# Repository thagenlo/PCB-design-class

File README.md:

# PCB-design-class
2.S975 KiCAD repo

**Multimeter Project**

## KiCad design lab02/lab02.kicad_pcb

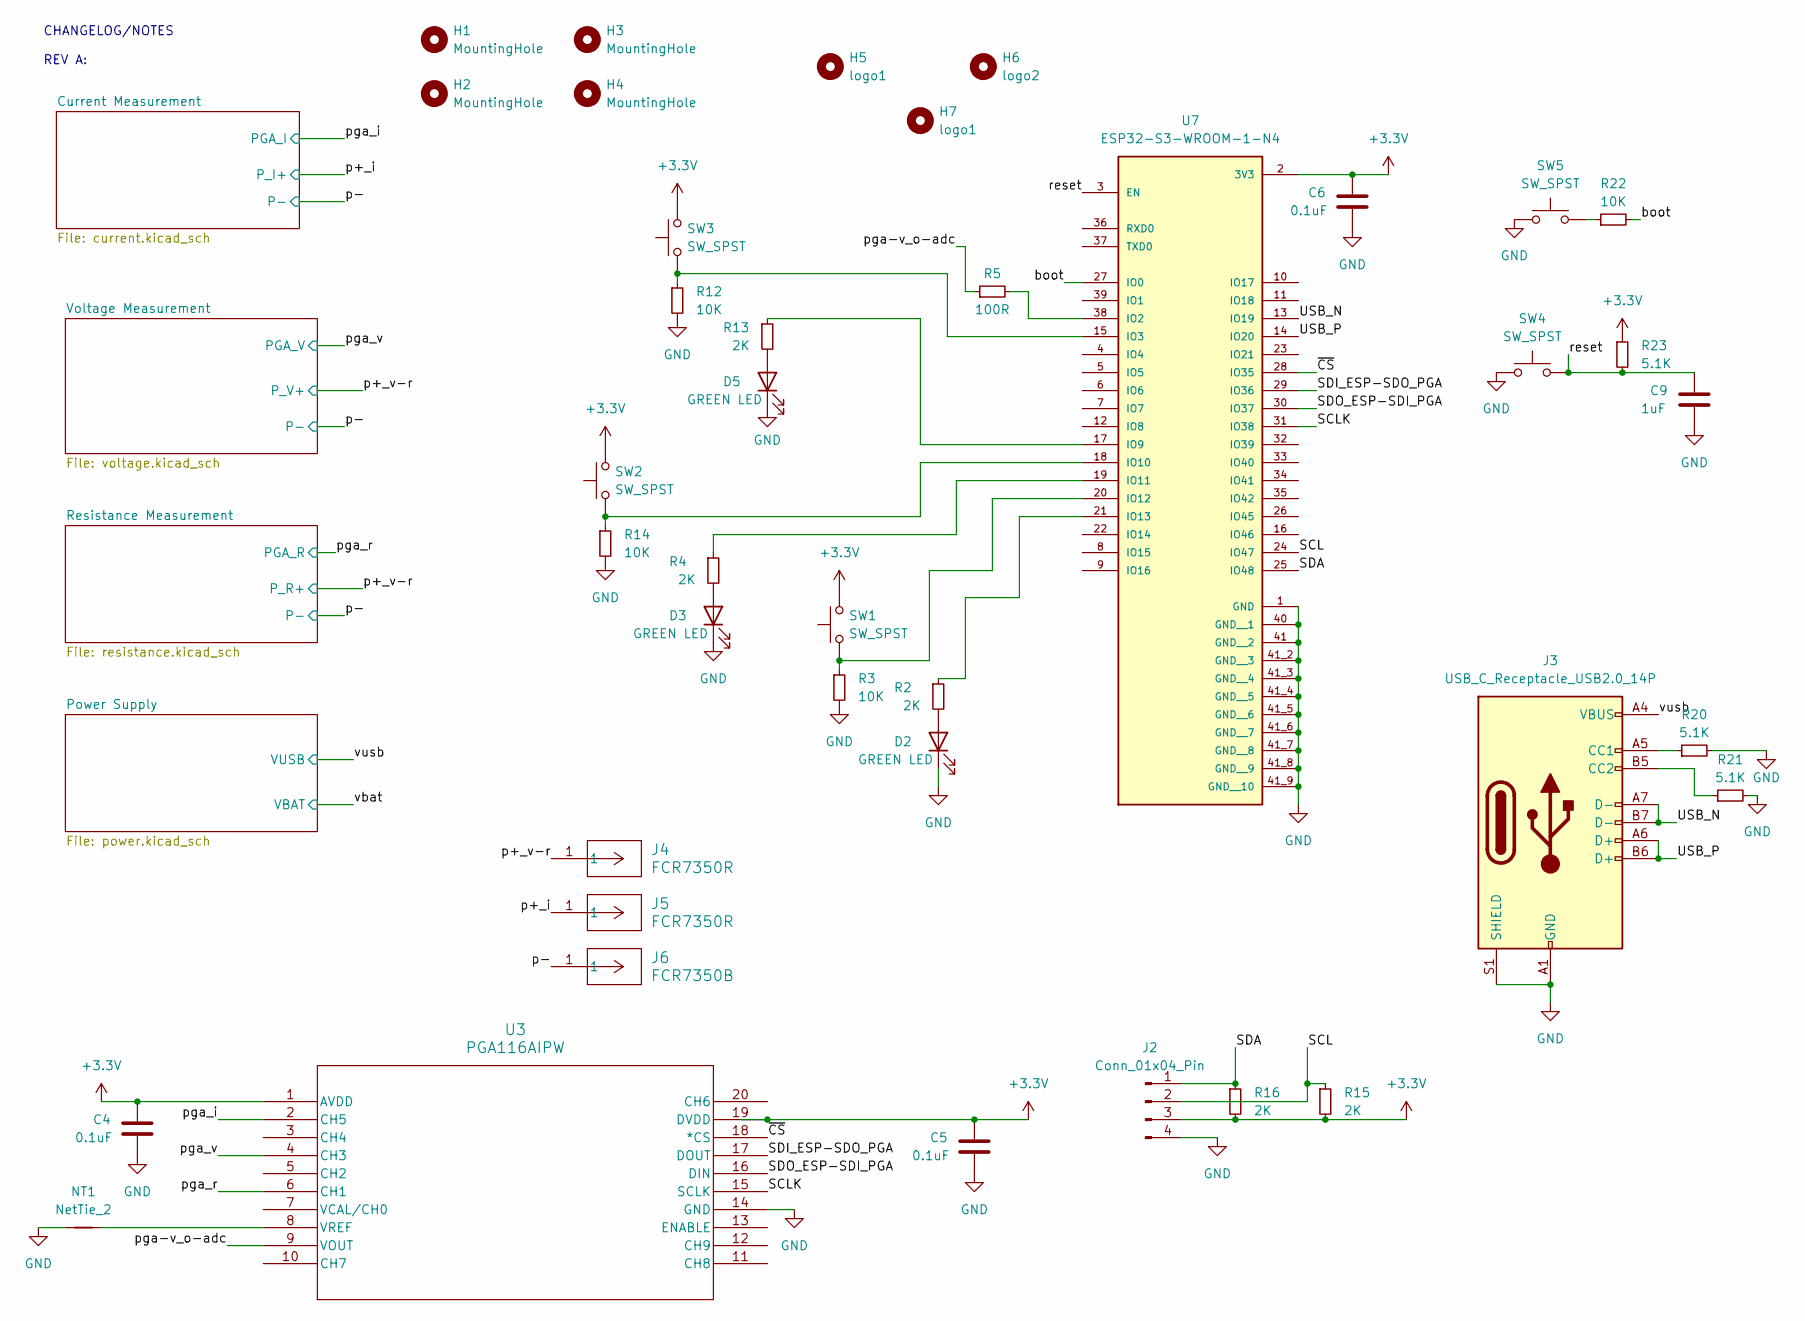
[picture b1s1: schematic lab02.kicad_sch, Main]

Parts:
C4, C5, C6: 0.1uF; C_0603_1608Metric
C9: 1uF; C_0603_1608Metric
D2, D3, D5: GREEN LED; LED_0603_1608Metric_Pad1.05x0.95mm_HandSolder; MPN LTST-C190GKT; Digikey PN 160-1183-1-ND
H1, H2, H3, H4: MountingHole; MountingHole_2.5mm
H5: logo1; EdgertonLogo
H6: logo2; EECSLogo
H7: logo1; MechE
J2: Conn_01x04_Pin; PPTC041LFBN-RC; MPN PPTC041LFBN-RC; Digikey PN S7002-ND
J3: USB_C_Receptacle_USB2.0_14P; USB_C_Receptacle_GCT_USB4085; MPN USB4085-GF-A; Digikey PN 2073-USB4085-GF-ACT-ND
J4, J5: FCR7350R; CONN1_FCR7350R_CLF; MPN FCR7350R; Digikey PN 4654-FCR7350R-ND
J6: FCR7350B; CONN1_FCR7350R_CLF; MPN FCR7350B; Digikey PN 4654-FCR7350B-ND
NT1: NetTie_2; NetTie-2_SMD_Pad0.5mm
R2, R4, R13, R15, R16: 2K; R_0603_1608Metric
R3, R12, R14, R22: 10K; R_0603_1608Metric
R5: 100R; R_0603_1608Metric
R20, R21, R23: 5.1K; R_0603_1608Metric
SW1, SW2, SW3, SW4, SW5: SW_SPST; SWITCH_FSMSM_TYC; MPN FSMSM; Digikey PN 450-1140-ND
U3: PGA116AIPW; PGA116AIPWR; MPN PGA116AIPWR; Digikey PN 296-23772-1-ND
U7: ESP32-S3-WROOM-1-N4; ESP32-S3-WROOM-1; PARTREV v1.0; Digikey PN 1965-ESP32-S3-WROOM-1-N4CT-ND

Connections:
+3.3V: C4.1, C5.1, C6.1, J2.3, R15.2, R16.2, R23.1, SW1.2, SW2.2, SW3.2, U3.1 (AVDD), U3.19 (DVDD), U7.2 (3V3); also elsewhere on the board
/SCL: J2.2, R15.1, U7.24 (IO47)
/SCLK: U3.15 (SCLK), U7.31 (IO38)
/SDA: J2.1, R16.1, U7.25 (IO48)
/SDI_ESP-SDO_PGA: U3.17 (DOUT), U7.29 (IO36)
/SDO_ESP-SDI_PGA: U3.16 (DIN), U7.30 (IO37)
/USB_N: J3.A7 (D-), J3.B7 (D-), U7.13 (IO19)
/USB_P: J3.A6 (D+), J3.B6 (D+), U7.14 (IO20)
/boot: R22.2, U7.27 (IO0)
/p+_i: J5.1; also elsewhere on the board
/p+_v-r: J4.1; also elsewhere on the board
/pga-v_o-adc: R5.1, U3.9 (VOUT)
/pga_i: U3.2 (CH5); also elsewhere on the board
/pga_r: U3.6 (CH1); also elsewhere on the board
/pga_v: U3.4 (CH3); also elsewhere on the board
/reset: C9.1, R23.2, SW4.2, U7.3 (EN)
/vusb: J3.A4 (VBUS), J3.A9 (VBUS), J3.B4 (VBUS), J3.B9 (VBUS); also elsewhere on the board
/~CS: U3.18 (*CS), U7.28 (IO35)
GND: C4.2, C5.2, C6.2, C9.2, D2.1 (K), D3.1 (K), D5.1 (K), J2.4, J3.A1 (GND), J3.A12 (GND), J3.B1 (GND), J3.B12 (GND), J3.S1 (SHIELD), J6.1, NT1.1, R3.2, R12.2, R14.2, R20.2, R21.2, SW4.1, SW5.1, U3.14 (GND), U7.1 (GND), U7.40 (GND__1), U7.41 (GND__2), U7.41_2 (GND__3), U7.41_3 (GND__4), U7.41_4 (GND__5), U7.41_5 (GND__6), U7.41_6 (GND__7), U7.41_7 (GND__8), U7.41_8 (GND__9), U7.41_9 (GND__10); also elsewhere on the board
unnamed: D2.2 (A), R2.2
unnamed: D3.2 (A), R4.2
unnamed: D5.2 (A), R13.2
unnamed: J3.A5 (CC1), R20.1
unnamed: J3.B5 (CC2), R21.1
unnamed: R22.1, SW5.2
unnamed: NT1.2, U3.8 (VREF)
unnamed: R5.2, U7.38 (IO2)
unnamed: R12.1, SW3.1, U7.15 (IO3)
unnamed: R13.1, U7.17 (IO9)
unnamed: R14.1, SW2.1, U7.18 (IO10)
unnamed: R4.1, U7.19 (IO11)
unnamed: R3.1, SW1.1, U7.20 (IO12)
unnamed: R2.1, U7.21 (IO13)

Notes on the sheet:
CHANGELOG/NOTES REV A:

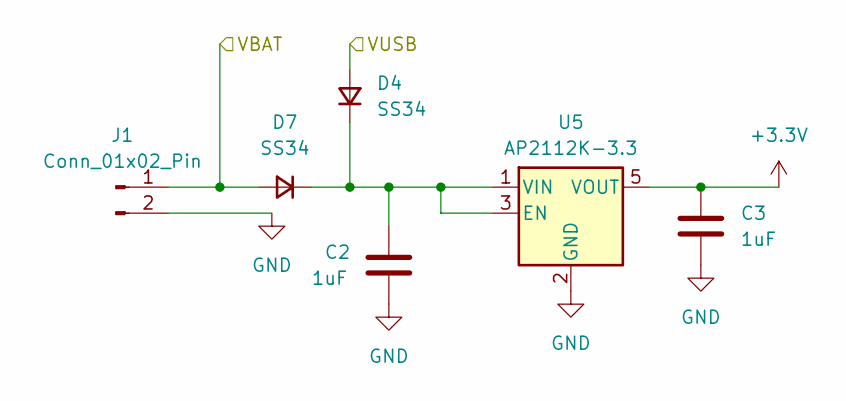
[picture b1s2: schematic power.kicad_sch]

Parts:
C2, C3: 1uF; C_0603_1608Metric
D4, D7: SS34; D_SMC
J1: Conn_01x02_Pin; JST_B2B-XH-A; MPN B2B-XH-A; Digikey PN 455-B2B-XH-A-ND
U5: AP2112K-3.3; SOT-23-5; MPN AP2112K-3.3TRG1; Digikey PN AP2112K-3.3TRG1DICT-ND

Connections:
+3.3V: C3.1, U5.5 (VOUT); also elsewhere on the board
/vbat: D7.2 (A), J1.1
/vusb: D4.2 (A); also elsewhere on the board
GND: C2.2, C3.2, J1.2, U5.2 (GND); also elsewhere on the board
unnamed: C2.1, D4.1 (K), D7.1 (K), U5.1 (VIN), U5.3 (EN)

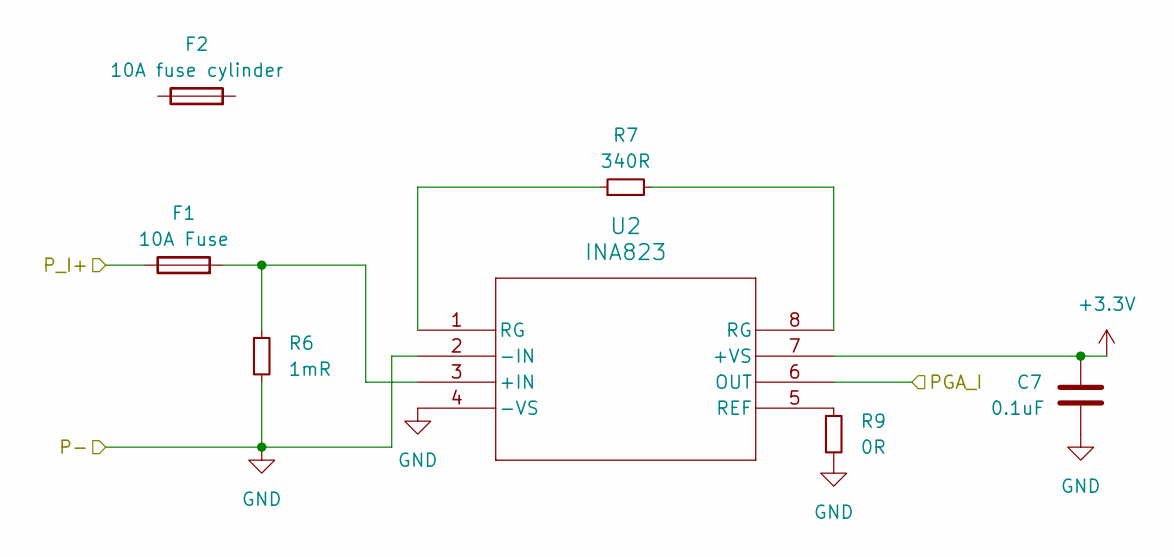
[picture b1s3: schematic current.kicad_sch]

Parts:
C7: 0.1uF; C_0603_1608Metric
F1: 10A Fuse; FUSE_31.8221_SCH; MPN 0031.8221; Digikey PN 486-1260-ND
F2: 10A fuse cylinder; MPN 7010.3530; Digikey PN 486-1865-ND
R6: 1mR; CSNL1206FT1L00; MPN CSNL1206FT1L00; Digikey PN CSNL1206FT1L00CT-ND
R7: 340R; R_0603_1608Metric
R9: 0R; R_0603_1608Metric
U2: INA823; SOIC-8_3.9x4.9mm_P1.27mm; MPN INA823DT; Digikey PN 296-INA823DTCT-ND

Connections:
+3.3V: C7.1, U2.7 (+VS); also elsewhere on the board
/p+_i: F1.1; also elsewhere on the board
/pga_i: U2.6 (OUT); also elsewhere on the board
GND: C7.2, R6.2, R9.2, U2.2 (-IN), U2.4 (-VS); also elsewhere on the board
unnamed: R7.1, U2.1 (RG)
unnamed: R7.2, U2.8 (RG)
unnamed: F1.2, R6.1, U2.3 (+IN)
unnamed: R9.1, U2.5 (REF)

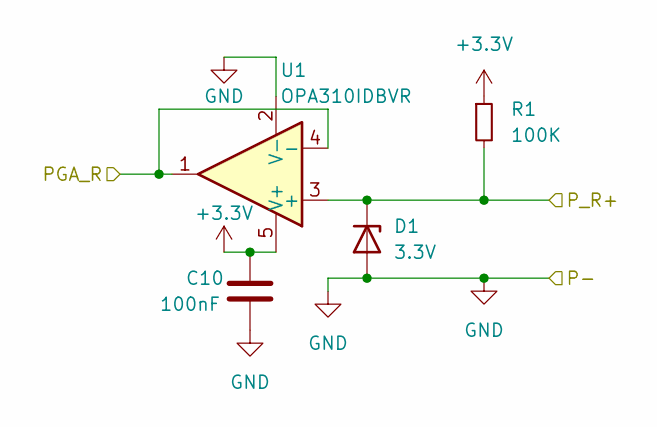
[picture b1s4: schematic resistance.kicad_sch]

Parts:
C10: 100nF; C_0603_1608Metric
D1: 3.3V; MMSZ4684T1G; MPN MMSZ4684T1G; Digikey PN MMSZ4684T1GOSCT-ND
R1: 100K; R_0603_1608Metric
U1: OPA310IDBVR; MPN OPA310IDBVR; Digikey PN 296-OPA310IDBVRCT-ND

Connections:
+3.3V: C10.1, R1.1, U1.5 (V+); also elsewhere on the board
/p+_v-r: D1.1 (K), R1.2, U1.3 (+); also elsewhere on the board
/pga_r: U1.1, U1.4 (-); also elsewhere on the board
GND: C10.2, D1.2 (A), U1.2 (V-); also elsewhere on the board

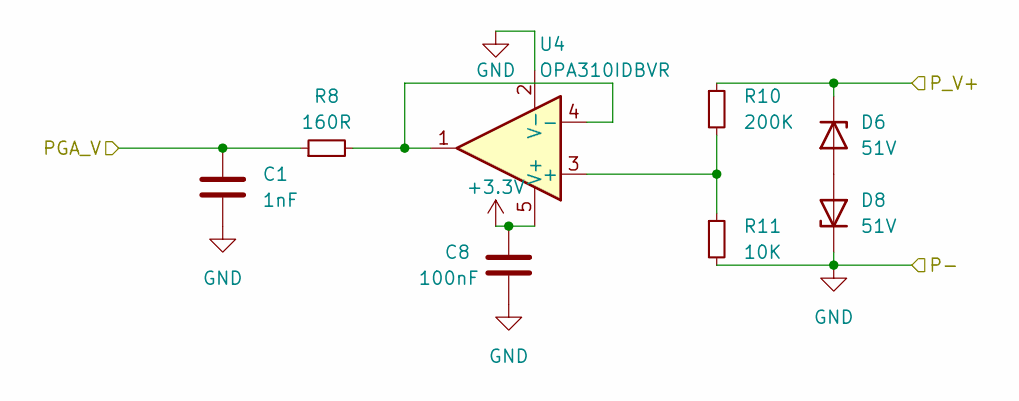
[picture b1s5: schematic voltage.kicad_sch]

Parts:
C1: 1nF; C_0603_1608Metric
C8: 100nF; C_0603_1608Metric
D6, D8: 51V; BZT52C51-7-F; MPN BZT52C51-7-F; Digikey PN BZT52C51-FDICT-ND
R8: 160R; R_0603_1608Metric
R10: 200K; R_0603_1608Metric
R11: 10K; R_0603_1608Metric
U4: OPA310IDBVR; MPN OPA310IDBVR; Digikey PN 296-OPA310IDBVRCT-ND

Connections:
+3.3V: C8.1, U4.5 (V+); also elsewhere on the board
/p+_v-r: D6.1 (K), R10.1; also elsewhere on the board
/pga_v: C1.1, R8.1; also elsewhere on the board
GND: C1.2, C8.2, D8.1 (K), R11.2, U4.2 (V-); also elsewhere on the board
unnamed: D6.2 (A), D8.2 (A)
unnamed: R10.2, R11.1, U4.3 (+)
unnamed: R8.2, U4.1, U4.4 (-)

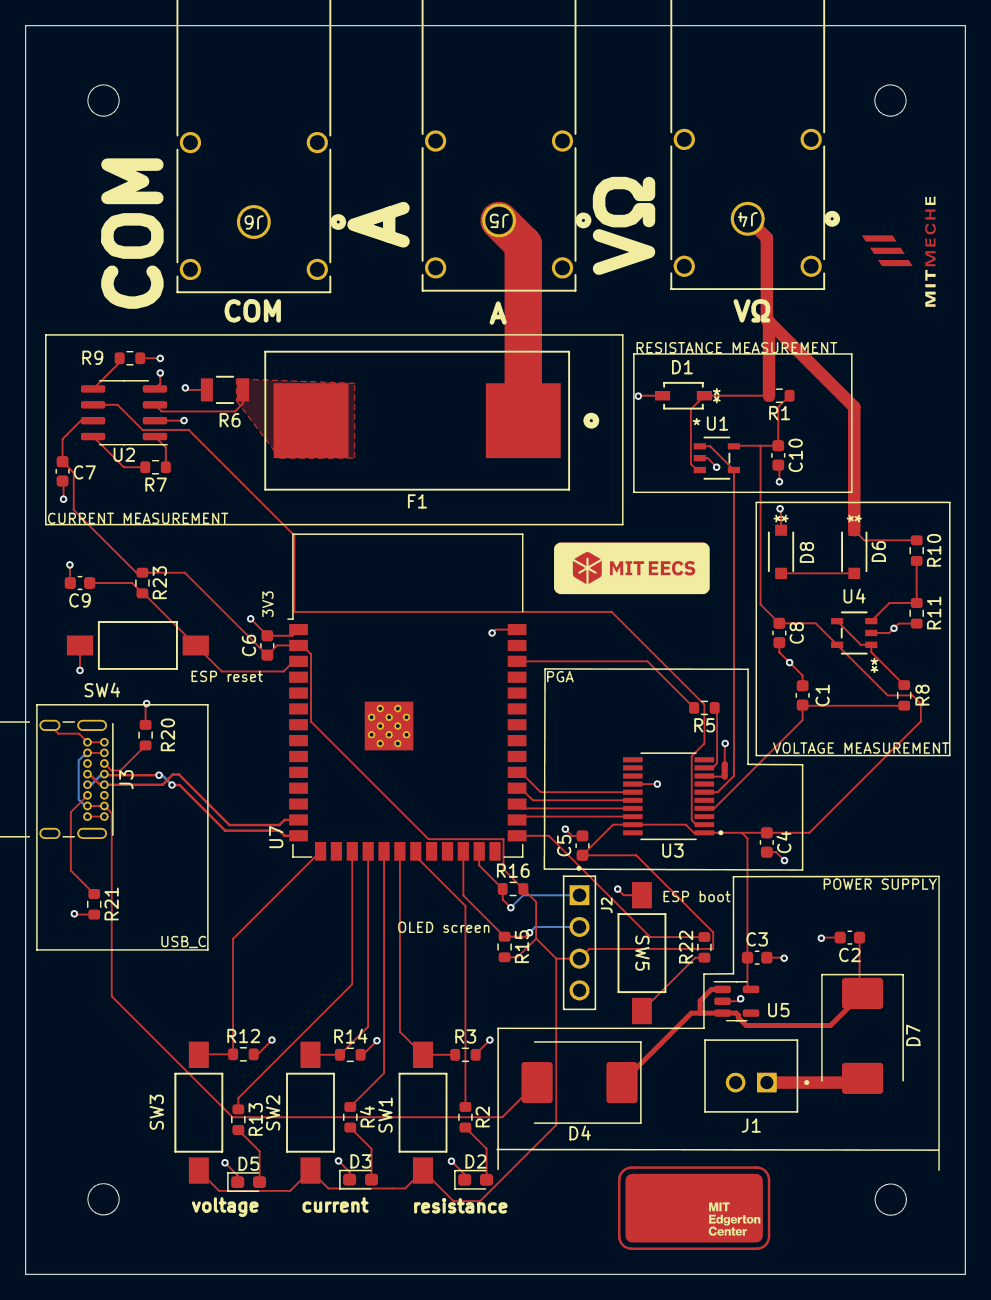
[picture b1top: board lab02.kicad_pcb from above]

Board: 2 copper layers, 75.3 x 100.0 mm, 64 parts (0 on the bottom side), 42 nets.

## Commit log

2024-01-11 set up
2024-01-11 main v0
2024-01-18 pcb layout v0
2024-01-18 pcb layout v1
2024-01-19 v7 pcb
